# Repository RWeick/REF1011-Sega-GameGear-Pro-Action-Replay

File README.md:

# REF1011-Sega-GameGear-Pro-Action-Replay
The JEDEC PAL dump, ROM dump, and Kicad PCB files for the Sega GameGear Pro Action Replay.

I acquired the ROM dump from the SMS Power forums user Apocalypse.

The PAL dump is made by me; it is a 1:1 of the original and varies slightly from the one made by Apocalypse. This is an actual dump of the chip, not a recreation.

The GameGear Pro Action Replay can now be produced from scratch. Happy Making.

PCB Thickness: 0.8 mm

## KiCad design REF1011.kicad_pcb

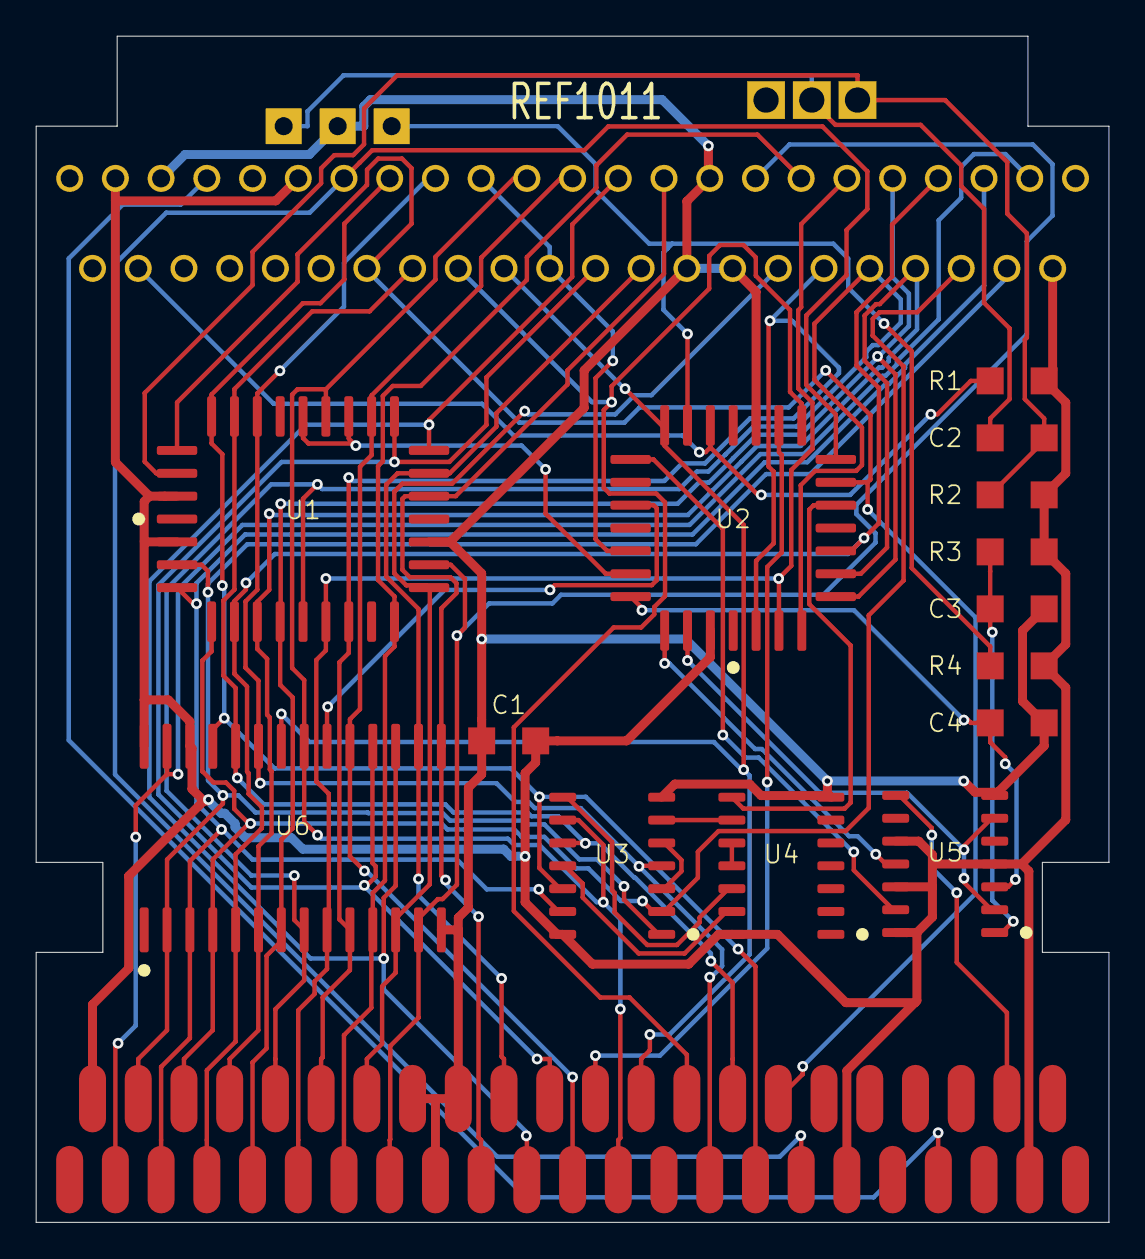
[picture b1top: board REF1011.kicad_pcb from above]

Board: 2 copper layers, 59.6 x 65.9 mm, 18 parts (0 on the bottom side), 49 nets.

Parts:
C1, C2, C3, C4: C_Small; SMD
J1: System Edge Connector
J2: Game Slot Connector; Cartridge Slot
R1, R2, R3, R4: R_Small_US; SMD
SW1: SW_SPDT; Switch
SW2: SW_Push; Button
U1: 27C256
U2: PALCE_20V8Q-25JC/4; PALCE 20V8Q
U3, U4: SN74HC32N; SOP-14
U5: 74HC74; SOP-14
U6: SRAM

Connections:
/1Y.Out: U3.3 (1Y), U3.5 (2B)
/4Y.Out: U4.10 (3B), U4.11 (4Y)
/+5V: C1.2, J1.2 (+5V), J1.35 (+5V), J1.43 (~TV), J2.2 (+5V), J2.35 (+5V), J2.43 (~TV), R1.2, R2.2, R3.2, R4.2, U1.2 (VPP), U1.32 (VCC), U2.28 (VCC), U3.14 (VCC), U4.14 (VCC), U5.4 (~S), U5.10 (~S), U5.12 (D), U5.14 (VCC), U6.26 (CS2), U6.28 (VCC)
/A0: J1.12 (A0), J2.12 (A0), U1.11 (A0), U2.2 (CLK/I_0), U6.10 (A0)
/A1: J1.11 (A1), J2.11 (A1), U1.10 (A1), U2.3 (I_1), U6.9 (A1)
/A2: J1.10 (A2), J2.10 (A2), U1.9 (A2), U2.4 (I_2), U6.8 (A2)
/A3: J1.9 (A3), J2.9 (A3), U1.8 (A3), U2.5 (I_3), U6.7 (A3)
/A4: J1.8 (A4), J2.8 (A4), U1.7 (A4), U2.6 (I_4), U6.6 (A4)
/A5: J1.7 (A5), J2.7 (A5), U1.6 (A5), U2.7 (I_5), U6.5 (A5)
/A6: J1.6 (A6), J2.6 (A6), U1.5 (A6), U3.2 (1B), U6.4 (A6)
/A6-A12: U2.9 (I_6), U4.8 (3Y)
/A6/A11/A12: U3.6 (2Y), U4.9 (3A)
/A7: J1.5 (A7), J2.5 (A7), U1.4 (A7), U3.13 (4B), U6.3 (A7)
/A7/A8: U3.11 (4Y), U4.13 (4B)
/A8: J1.31 (A8), J2.31 (A8), U1.29 (A8), U3.12 (4A), U6.25 (A8)
/A9: J1.30 (A9), J2.30 (A9), U1.28 (A9), U3.10 (3B), U6.24 (A9)
/A9/A10: U3.8 (3Y), U4.12 (4A)
/A10: J1.25 (A10), J2.25 (A10), U1.24 (A10), U3.9 (3A), U6.21 (A10)
/A11: J1.29 (A11), J2.29 (A11), U1.27 (A11), U3.4 (2A), U6.23 (A11)
/A12: J1.4 (A12), J2.4 (A12), U1.3 (A12), U3.1 (1A), U6.2 (A12)
/A13: J1.32 (A13), J2.32 (A13), U1.30 (A13), U2.10 (I_7)
/A14: J1.33 (A14), J2.33 (A14), U2.11 (I_8)
/A15: J1.28 (A15), J2.28 (A15), U2.12 (I_9)
/D0: J1.13 (D0), J2.13 (D0), U1.13 (D0), U6.11 (I/O1)
/D1: J1.14 (D1), J2.14 (D1), U1.14 (D1), U6.12 (I/O2)
/D2: J1.15 (D2), J2.15 (D2), U1.15 (D2), U6.13 (I/O3)
/D3: J1.19 (D3), J2.19 (D3), U1.18 (D3), U6.15 (I/O4)
/D4: J1.20 (D4), J2.20 (D4), U1.19 (D4), U6.16 (I/O5)
/D5: J1.21 (D5), J2.21 (D5), U1.20 (D5), U6.17 (I/O6)
/D6: J1.22 (D6), J2.22 (D6), U1.21 (D6), U6.18 (I/O7)
/D7: J1.23 (D7), J2.23 (D7), U1.22 (D7), U6.19 (I/O8)
/EEPROM.A14: C2.2, R2.1, SW2.2, U1.31 (A14)
/GND: C1.1, C3.2, C4.2, J1.16 (GND), J1.17 (GND), J1.18 (GND), J2.16 (GND), J2.17 (GND), J2.18 (GND), J2.41 (GND), SW1.2 (B), U1.16 (GND), U2.14 (GND), U3.7 (GND), U4.7 (GND), U5.7 (GND), U6.14 (GND)
/High.Pull: C3.1, R3.1, U5.1 (~R)
/Low.Pull: C2.1, SW1.1 (A), SW2.1
/Switch: R4.1, SW1.3 (C), U2.17 (I_12)
/U5A.C: C4.1, U2.25 (I/O_6), U5.3 (C)
/U5A.D&~Q: U2.27 (I_13), U5.2 (D), U5.6 (~Q)
/U5B.C: U2.26 (I/O_7), U5.11 (C)
/U5B.~R: U2.19 (I/O_1), U5.13 (~R)
/~CE.Game: J2.24 (~CE), J2.27 (~M0-7), U2.23 (I/O_4)
/~CE.Sys: J1.24 (~CE), U2.13 (I_10)
/~EEPROM.CE&OE: U1.23 (~CE), U1.25 (~OE), U2.24 (I/O_5)
/~GG.Game: J2.42 (~GG), R1.1, U2.16 (OE/I_11)
/~GG.Sys: J1.42 (~GG), U5.8 (~Q)
/~Read: J1.26 (~Read), J2.26 (~Read), U2.18 (I/O_0), U6.22 (~OE)
/~Reset: J1.39 (~Reset), J2.39 (~Reset)
/~SRAM.CE: U2.21 (I/O_3), U6.20 (~CS1)
/~Write: J1.3 (~Write), J2.3 (~Write), U6.27 (~WE)
